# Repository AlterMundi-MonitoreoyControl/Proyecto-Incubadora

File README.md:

# LibreIncu 

[Manual de montaje](docs/index.md) · [Descargar PDF](docs/manual_libreincu_150.pdf)

Is an innovative project aimed at enhancing the efficiency and productivity of poultry incubators in family farming. Developed by Asociación Civil AlterMundi and CTO, this system integrates advanced monitoring and control technologies to optimize temperature and humidity levels, reducing manual labor and increasing hatch rates. Utilizing free hardware and software, the project promotes sustainable agricultural practices and empowers local communities with technical skills. Join us in revolutionizing family farming with technology!

Each incubator broadcasts a Wi-Fi network with a name that starts with “incu-” followed by a number. A user who wants to control their incubator can connect to this Wi-Fi network and change the incubator paramteres using the android app. Additionally, each incubator also connects to an external Wi-Fi network to send data over the internet to a remote Grafana server.

## LibreIncu en los medios
Aquí encontrarás enlaces a 

### Notas y artículos periodísticos 
Tiempo Argentino.Tiempo Rural.

Crean “LibreIncu”, una incubadora para familias productoras que funciona con software libre
https://bit.ly/LibreIncu

Pagina 12.

Problemas en la salud, maltrato animal y pérdida de soberanía. ¿Qué hacer con la industria avícola?
https://www.pagina12.com.ar/798691-que-hacer-con-la-industria-avicola

Multimedio Comechingones: 

INCUBADORAS LIBRES Y LA SOBERANÍA ALIMENTARIA Y TECNOLÓGICA.
https://www.youtube.com/watch?v=XAIEJV1IsmM

Radio Pueblo 103.3

Somos Tierra (programa) 07/03
“LibreIncu”, una incubadora para familias productoras que funciona con software libre.
https://www.facebook.com/100064102022746/posts/pfbid0N8CtLHdo2AVj12pVsAtcoeShCmByB2GCyXqmLqw75aoo8GYHFhkMTCCCVQQF8PBvl/?app=fbl

CDM Noticias: 

👉🏽En una entrevista radial con CDM Noticias, Fabricio Puzio, integrante de la organización rural CTO y uno de los impulsores del proyecto, brindó detalles del proyecto
https://cdmnoticias.com.ar/2025/03/11/libreincu-una-incubadora-de-pollos-con-software-libre-para-la-agricultura-familiar-en-cordoba/

### Videos

En este video encontrarán las voces de las comunidades que recibieron la incubadora en 1ra persona:
Youtube: https://youtu.be/KnWVigydmrw
Drive (para descarga archivo):
https://drive.google.com/file/d/1XJGJvUBiZXpjTJCaMYPYS3Le8TjS4YHT/view?usp=drive_link

Este video resume la actividad de febrero de 2025, dónde se realizó una capacitación técnica sobre el uso de la incubadora y su entrega a las comunidades:
Youtube: https://youtu.be/x1D_cCt7HYg
Drive (archivo):
https://drive.google.com/file/d/1NNPJ5_CfbWtDd18YyunTMB_yW_l8wr9t/view?usp=drive_link

En este video, encontrarán las voces del Equipo de Altermundi, reflexionando sobre el proceso de desarrollo.
Youtube: https://youtu.be/SZky4Ak8hUw
Drive (archivo):
https://drive.google.com/file/d/1BhJ7BwKUeTCceVNzBBIgxEsvleegejvH/view?usp=drive_link

En este video encontrarán testimonios sobre lo que implica el proyecto de desarrollo para las organizaciones involucradas.
Youtube: https://youtu.be/OzdKqgwdBYY

En este video encontrarán una presentación técnica Incubadora, con sus componentes:
https://www.youtube.com/watch?v=WrC1Y-ACtMo
Corte cuadrado 1:
https://drive.google.com/file/d/1Y_UQ-bno3-HFeVKtA_xg6CsesUtA-4hE/view?usp=drive_link
Corte cuadrado 2:
https://drive.google.com/file/d/13rHx7xk9e1rThg5PIM3QHikm3YS5sNPg/view?usp=drive_link

En este video encontrarán testimonios sobre la 1er Capacitación realizada con las comunidades sobre manejo productivo de huevos fértiles e incubadora.
https://youtu.be/IfGGvOIJ1b8
https://drive.google.com/file/d/1ajWQofPJQxNfXo5LtOdFrOzkCoTbWGiC/view?usp=sharing

## made with :heart: by:

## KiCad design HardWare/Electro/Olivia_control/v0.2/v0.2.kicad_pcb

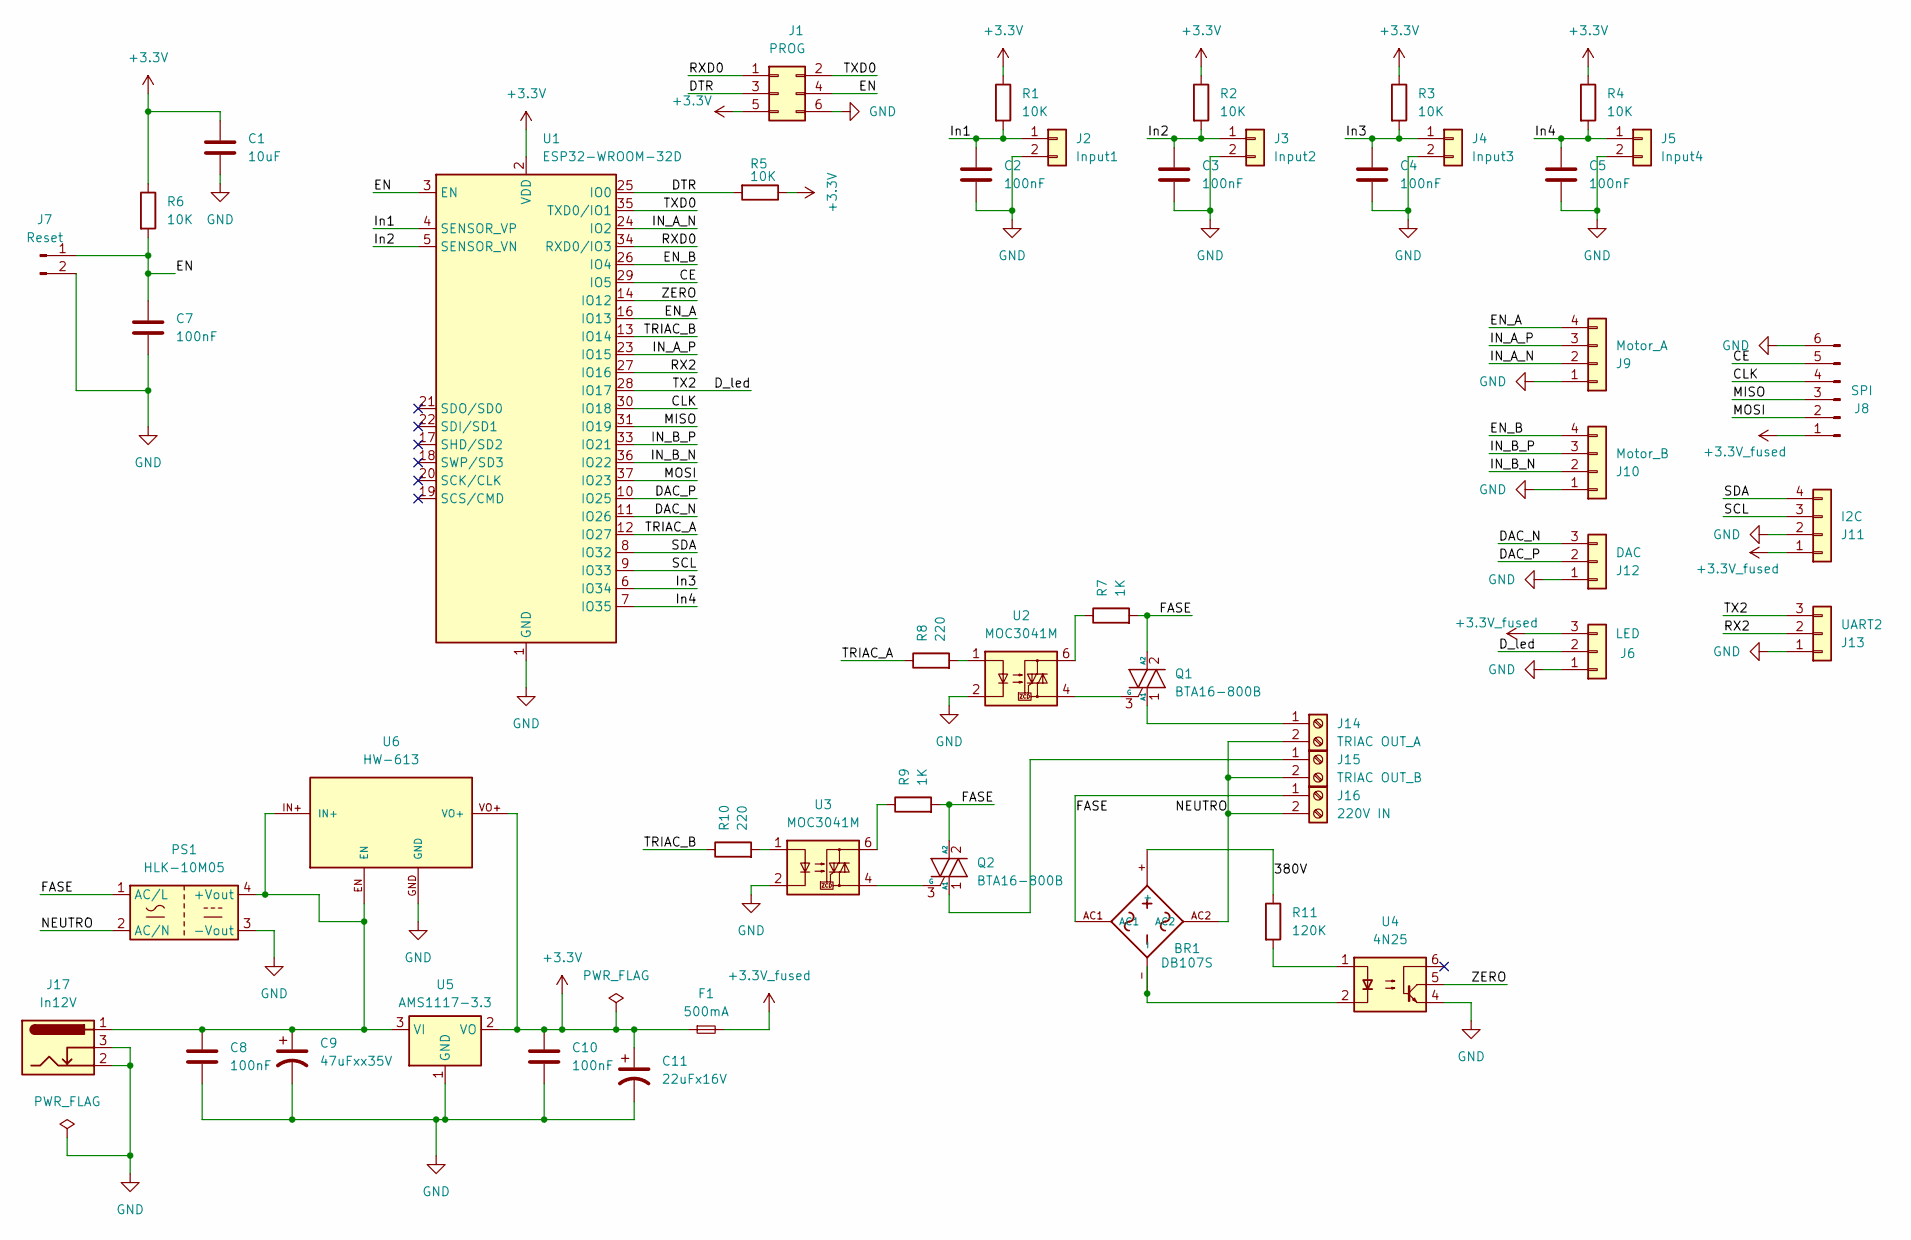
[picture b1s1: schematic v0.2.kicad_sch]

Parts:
BR1: DB107S; DIOB_DB107S; DigiKey_Part_Number 1655-DB107STR-ND
C1: 10uF; C_0805_2012Metric_Pad1.18x1.45mm_HandSolder
C2, C3, C4, C5, C7, C8, C10: 100nF; C_0805_2012Metric_Pad1.18x1.45mm_HandSolder
C9: 47uFxx35V; CP_EIA-6032-28_Kemet-C_Pad2.25x2.35mm_HandSolder
C11: 22uFx16V; CP_EIA-6032-28_Kemet-C_Pad2.25x2.35mm_HandSolder
F1: 500mA; Fuse_1206_3216Metric_Pad1.42x1.75mm_HandSolder
J1: PROG; PinHeader_2x03_P2.54mm_Vertical
J2: Input1; Molex_SL_171971-0002_1x02_P2.54mm_Vertical
J3: Input2; Molex_SL_171971-0002_1x02_P2.54mm_Vertical
J4: Input3; Molex_SL_171971-0002_1x02_P2.54mm_Vertical
J5: Input4; Molex_SL_171971-0002_1x02_P2.54mm_Vertical
J6: LED; Molex_SL_171971-0003_1x03_P2.54mm_Vertical
J7: Reset; PinHeader_1x02_P2.54mm_Vertical
J8: SPI; PinHeader_1x06_P2.54mm_Vertical
J9: Motor_A; Molex_SL_171971-0004_1x04_P2.54mm_Vertical
J10: Motor_B; Molex_SL_171971-0004_1x04_P2.54mm_Vertical
J11: I2C; Molex_SL_171971-0004_1x04_P2.54mm_Vertical
J12: DAC; Molex_SL_171971-0003_1x03_P2.54mm_Vertical
J13: UART2; Molex_SL_171971-0003_1x03_P2.54mm_Vertical
J14: TRIAC OUT_A; PhoenixContact_GMSTBA_2,5_2-G-7,62_1x02_P7.62mm_Horizontal
J15: TRIAC OUT_B; PhoenixContact_GMSTBA_2,5_2-G-7,62_1x02_P7.62mm_Horizontal
J16: 220V IN; PhoenixContact_GMSTBA_2,5_2-G-7,62_1x02_P7.62mm_Horizontal
J17: In12V; BarrelJack_Horizontal
PS1: HLK-10M05; Converter_ACDC_Hi-Link_HLK-10Mxx
Q1, Q2: BTA16-800B; TO-220-3_Vertical
R1, R2, R3, R4, R5, R6: 10K; R_0805_2012Metric_Pad1.20x1.40mm_HandSolder
R7, R9: 1K; R_0805_2012Metric_Pad1.20x1.40mm_HandSolder
R8, R10: 220; R_0805_2012Metric_Pad1.20x1.40mm_HandSolder
R11: 120K; R_0805_2012Metric_Pad1.20x1.40mm_HandSolder
U1: ESP32-WROOM-32D
U2, U3: MOC3041M; SMDIP-6_W9.53mm
U4: 4N25; SMDIP-6_W9.53mm
U5: AMS1117-3.3; SOT-223-3_TabPin2
U6: HW-613

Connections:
+3.3V: C1.1, C10.1, C11.1, F1.1, J1.5, R1.1, R2.1, R3.1, R4.1, R5.1, R6.1, U1.2 (VDD), U5.2 (VO), U6.VO+
+3.3V_fused: F1.2, J6.3, J8.1, J11.1
/380V: BR1.+, R11.1
/CE: J8.5, U1.29 (IO5)
/CLK: J8.4, U1.30 (IO18)
/DAC_N: J12.3, U1.11 (IO26)
/DAC_P: J12.2, U1.10 (IO25)
/DTR: J1.3, R5.2, U1.25 (IO0)
/D_led: J6.2, J13.3, U1.28 (IO17)
/EN: C7.1, J1.4, J7.1, R6.2, U1.3 (EN)
/EN_A: J9.4, U1.16 (IO13)
/EN_B: J10.4, U1.26 (IO4)
/FASE: BR1.AC1, J16.1, PS1.1 (AC/L), Q1.2 (A2), Q2.2 (A2), R7.2, R9.2
/IN_A_N: J9.2, U1.24 (IO2)
/IN_A_P: J9.3, U1.23 (IO15)
/IN_B_N: J10.2, U1.36 (IO22)
/IN_B_P: J10.3, U1.33 (IO21)
/In1: C2.1, J2.1, R1.2, U1.4 (SENSOR_VP)
/In2: C3.1, J3.1, R2.2, U1.5 (SENSOR_VN)
/In3: C4.1, J4.1, R3.2, U1.6 (IO34)
/In4: C5.1, J5.1, R4.2, U1.7 (IO35)
/MISO: J8.3, U1.31 (IO19)
/MOSI: J8.2, U1.37 (IO23)
/NEUTRO: BR1.AC2, J14.2, J15.2, J16.2, PS1.2 (AC/N)
/RX2: J13.2, U1.27 (IO16)
/RXD0: J1.1, U1.34 (RXD0/IO3)
/SCL: J11.3, U1.9 (IO33)
/SDA: J11.4, U1.8 (IO32)
/TRIAC_A: R8.1, U1.12 (IO27)
/TRIAC_B: R10.1, U1.13 (IO14)
/TXD0: J1.2, U1.35 (TXD0/IO1)
/ZERO: U1.14 (IO12), U4.5, U4.6
GND: C1.2, C2.2, C3.2, C4.2, C5.2, C7.2, C8.2, C9.2, C10.2, C11.2, J1.6, J2.2, J3.2, J4.2, J5.2, J6.1, J7.2, J8.6, J9.1, J10.1, J11.2, J12.1, J13.1, J17.2, J17.3, PS1.3 (-Vout), U1.1 (GND), U1.15 (GND), U1.38 (GND), U1.39 (GND), U2.2, U3.2, U4.4, U5.1 (GND), U6.GND
unnamed: J14.1, Q1.1 (A1)
unnamed: J15.1, Q2.1 (A1)
unnamed: C8.1, C9.1, J17.1, PS1.4 (+Vout), U5.3 (VI), U6.EN, U6.IN+
unnamed: Q1.3 (G), U2.4
unnamed: Q2.3 (G), U3.4
unnamed: R7.1, U2.6
unnamed: R8.2, U2.1
unnamed: R9.1, U3.6
unnamed: R10.2, U3.1
unnamed: R11.2, U4.1

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
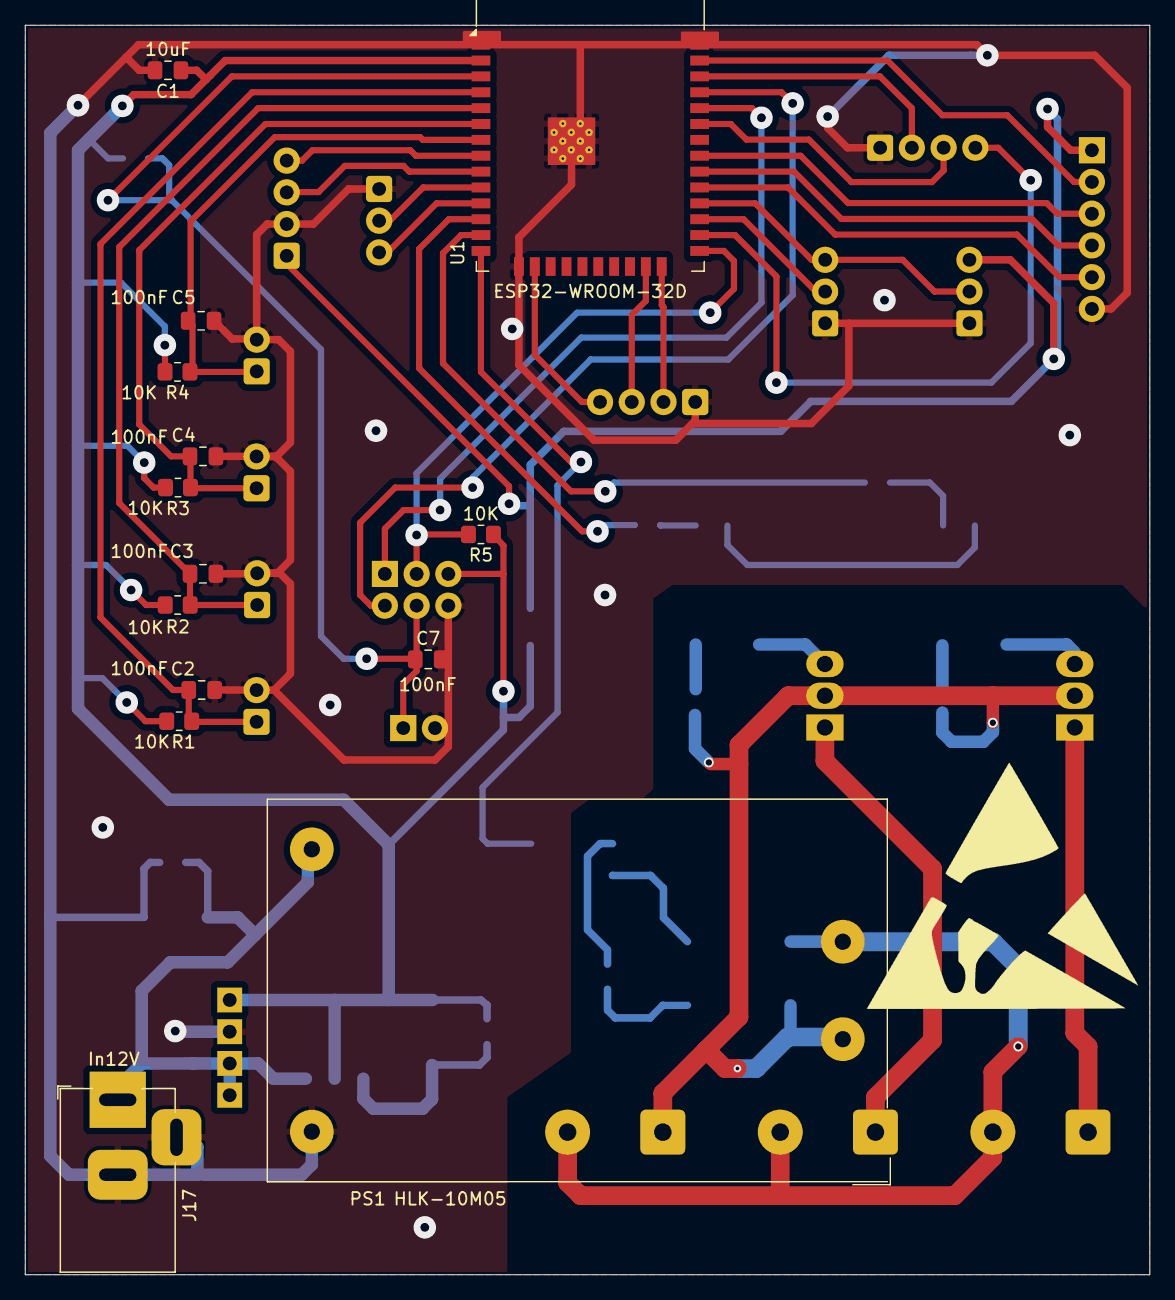
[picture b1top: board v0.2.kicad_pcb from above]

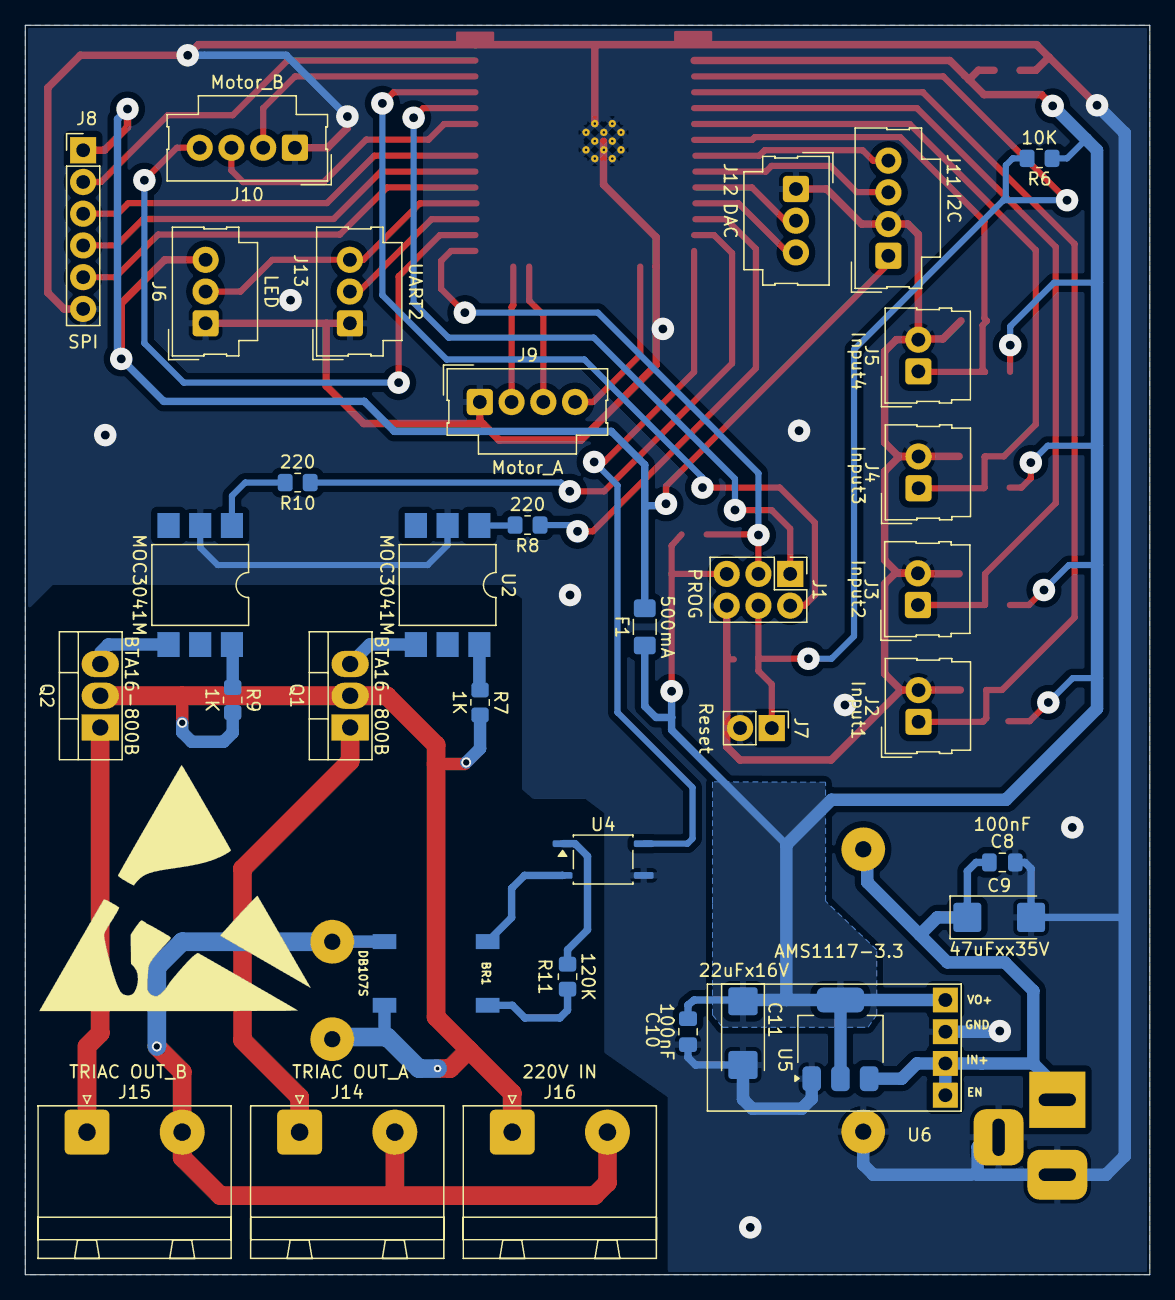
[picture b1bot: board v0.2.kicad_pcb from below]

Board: 2 copper layers, 90.0 x 100.0 mm, 49 parts (35 on the bottom side), 44 nets.

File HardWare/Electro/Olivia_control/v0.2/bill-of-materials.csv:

"Reference","Value","Footprint","Qty"
"BR1","DB107S","lib:DIOB_DB107S","1"
"C1","10uF","Capacitor_SMD:C_0805_2012Metric_Pad1.18x1.45mm_HandSolder","1"
"C2,C3,C4,C5,C7,C8,C10","100nF","Capacitor_SMD:C_0805_2012Metric_Pad1.18x1.45mm_HandSolder","7"
"C9","47uFxx35V","Capacitor_Tantalum_SMD:CP_EIA-6032-28_Kemet-C_Pad2.25x2.35mm_HandSolder","1"
"C11","22uFx16V","Capacitor_Tantalum_SMD:CP_EIA-6032-28_Kemet-C_Pad2.25x2.35mm_HandSolder","1"
"F1","500mA","Fuse:Fuse_1206_3216Metric_Pad1.42x1.75mm_HandSolder","1"
"J1","PROG","Connector_PinHeader_2.54mm:PinHeader_2x03_P2.54mm_Vertical","1"
"J2","Input1","Connector_Molex:Molex_SL_171971-0002_1x02_P2.54mm_Vertical","1"
"J3","Input2","Connector_Molex:Molex_SL_171971-0002_1x02_P2.54mm_Vertical","1"
"J4","Input3","Connector_Molex:Molex_SL_171971-0002_1x02_P2.54mm_Vertical","1"
"J5","Input4","Connector_Molex:Molex_SL_171971-0002_1x02_P2.54mm_Vertical","1"
"J6","LED","Connector_Molex:Molex_SL_171971-0003_1x03_P2.54mm_Vertical","1"
"J7","Reset","Connector_PinHeader_2.54mm:PinHeader_1x02_P2.54mm_Vertical","1"
"J8","SPI","Connector_PinHeader_2.54mm:PinHeader_1x06_P2.54mm_Vertical","1"
"J9","Motor_A","Connector_Molex:Molex_SL_171971-0004_1x04_P2.54mm_Vertical","1"
"J10","Motor_B","Connector_Molex:Molex_SL_171971-0004_1x04_P2.54mm_Vertical","1"
"J11","I2C","Connector_Molex:Molex_SL_171971-0004_1x04_P2.54mm_Vertical","1"
"J12","DAC","Connector_Molex:Molex_SL_171971-0003_1x03_P2.54mm_Vertical","1"
"J13","UART2","Connector_Molex:Molex_SL_171971-0003_1x03_P2.54mm_Vertical","1"
"J14","TRIAC OUT_A","Connector_Phoenix_GMSTB:PhoenixContact_GMSTBA_2,5_2-G-7,62_1x02_P7.62mm_Horizontal","1"
"J15","TRIAC OUT_B","Connector_Phoenix_GMSTB:PhoenixContact_GMSTBA_2,5_2-G-7,62_1x02_P7.62mm_Horizontal","1"
"J16","220V IN","Connector_Phoenix_GMSTB:PhoenixContact_GMSTBA_2,5_2-G-7,62_1x02_P7.62mm_Horizontal","1"
"J17","In12V","Connector_BarrelJack:BarrelJack_Horizontal","1"
"Q1,Q2","BTA16-800B","Package_TO_SOT_THT:TO-220-3_Vertical","2"
"R1,R2,R3,R4,R5,R6","10K","Resistor_SMD:R_0805_2012Metric_Pad1.20x1.40mm_HandSolder","6"
"R7,R9","1K","Resistor_SMD:R_0805_2012Metric_Pad1.20x1.40mm_HandSolder","2"
"R8,R10","220","Resistor_SMD:R_0805_2012Metric_Pad1.20x1.40mm_HandSolder","2"
"R11","120K","Resistor_SMD:R_0805_2012Metric_Pad1.20x1.40mm_HandSolder","1"
"U1","ESP32-WROOM-32D","RF_Module:ESP32-WROOM-32D","1"
"U2,U3","MOC3041M","Package_DIP:SMDIP-6_W9.53mm","2"
"U4","4N25","Package_DIP:SMDIP-6_W9.53mm","1"
"U6","HW-613","Connector_PinHeader_2.54mm:PinHeader_1x04_P2.54mm_Vertical","1"

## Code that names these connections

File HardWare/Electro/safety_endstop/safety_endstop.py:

#!/usr/bin/env python3
"""Esquemas del final de carrera de seguridad para el motor de volteo.

Agrega DOS finales de carrera (NC, normalmente cerrados) en serie con las
entradas logicas IN1 e IN2 del puente H, en paralelo a los reed switches que
ya usa el firmware (GPIO35 / GPIO34). Es un enclavamiento por HARDWARE: corta
la marcha aunque el firmware o el reed fallen (sobre-recorrido).

Comportamiento DIRECCIONAL:
  - FC-SUP (tope superior) corta IN1 (subir) y deja libre IN2 (bajar).
  - FC-INF (tope inferior) corta IN2 (bajar) y deja libre IN1 (subir).
  => al pisar un tope el motor NO avanza en esa direccion pero puede revertir
     para salir del fin de carrera.

Genera SVG con schemkit (repo vecino). Correr con el venv de schemkit:
    /home/pablo/repos/schemkit/.venv/bin/python safety_endstop.py
"""

import os
import sys

# schemkit (repo vecino) — agregar su raiz por si no esta instalado en el venv
sys.path.insert(0, '/home/pablo/repos/schemkit')

import schemdraw
import schemdraw.elements as elm
from schemdraw import flow

from schemkit import (
    CONFIG, add_title, add_footer,
    C_GPIO, C_VCC, C_GND, C_WARN, C_ADC, NOTE_COLOR,
)

OUT = os.path.join(os.path.dirname(os.path.abspath(__file__)), 'schematics')
os.makedirs(OUT, exist_ok=True)


# ---------------------------------------------------------------------------
# 1. Enclavamiento de seguridad: corte direccional de IN1 / IN2
# ---------------------------------------------------------------------------
def draw_safety_interlock():
    with schemdraw.Drawing(file=os.path.join(OUT, 'sch_safety_endstop.svg'),
                           show=False) as d:
        d.config(**CONFIG)

        # === ESP32 — 3 salidas hacia el puente H ===
        esp = d.add(elm.Ic(
            pins=[
                elm.IcPin(name='IN_A_N', anchorname='IN1', side='right', slot='3/3'),
                elm.IcPin(name='IN_A_P', anchorname='IN2', side='right', slot='2/3'),
                elm.IcPin(name='EN_A',   anchorname='EN',  side='right', slot='1/3'),
            ],
            edgepadW=2.8, edgepadH=1.2, pinspacing=3.4, lsize=11,
        ).label('Motor_A / J9\n(placa Olivia)', loc='center', fontsize=10))

        # GPIO de origen (en el ESP32) que sale por cada pin del conector Motor_A
        d.add(elm.Label().at((esp.IN1[0] - 0.3, esp.IN1[1] + 0.55))
              .label('pin2 · GPIO2', fontsize=7, color=NOTE_COLOR, halign='right'))
        d.add(elm.Label().at((esp.IN2[0] - 0.3, esp.IN2[1] + 0.55))
              .label('pin3 · GPIO15', fontsize=7, color=NOTE_COLOR, halign='right'))
        d.add(elm.Label().at((esp.EN[0] - 0.3, esp.EN[1] + 0.55))
              .label('pin4 · EN_A', fontsize=7, color=NOTE_COLOR, halign='right'))

        # === Puente H — alineado pin a pin con el ESP32 ===
        GAP = 11
        hb = d.add(elm.Ic(
            pins=[
                elm.IcPin(name='IN1',  anchorname='HIN1', side='left',  slot='3/3'),
                elm.IcPin(name='IN2',  anchorname='HIN2', side='left',  slot='2/3'),
                elm.IcPin(name='EN',   anchorname='HEN',  side='left',  slot='1/3'),
                elm.IcPin(name='OUT1', anchorname='OUT1', side='right', slot='2/2'),
                elm.IcPin(name='OUT2', anchorname='OUT2', side='right', slot='1/2'),
            ],
            edgepadW=1.2, edgepadH=1.2, pinspacing=3.4, lsize=11,
        ).at((esp.IN1[0] + GAP, esp.IN1[1])).anchor('HIN1')
         .label('Puente H\n(modulo)', loc='center', fontsize=10))

        # --- Helper: tramo IN con final de carrera NC + pull-down ---
        def in_line_with_endstop(esp_pin, hb_pin, fc_label, in_label):
            seg = 2.8          # tramo ESP -> switch
            sw_len = 1.9       # largo del switch
            # tramo desde el pin del ESP
            d.add(elm.Line().at(esp_pin).right(seg).color(C_GPIO)
                  .label(in_label, loc='top', fontsize=8))
            # final de carrera NC (normalmente cerrado) en serie
            sw = d.add(elm.Switch(nc=True).right().length(sw_len).color(C_WARN)
                       .label(fc_label, loc='top', fontsize=8, color=C_WARN))
            node = sw.end
            d.add(elm.Dot().at(node))
            # continua hasta la entrada del puente H
            d.add(elm.Line().at(node).tox(hb_pin[0]).color(C_GPIO))
            # pull-down 10k: deja la entrada en 0 (motor parado) si el FC abre.
            # Cae dentro del hueco bajo su propia linea (no cruza las demas).
            d.add(elm.Resistor().at(node).down(1.6)
                  .label('10k', loc='right', fontsize=8))
            d.add(elm.Ground())
            return node

        # IN1 = IN_A_N (J9 pin2, subir): cortado por el tope SUPERIOR
        in_line_with_endstop(esp.IN1, hb.HIN1, 'FC-SUP (NC)', 'IN_A_N  subir')
        # IN2 = IN_A_P (J9 pin3, bajar): cortado por el tope INFERIOR
        in_line_with_endstop(esp.IN2, hb.HIN2, 'FC-INF (NC)', 'IN_A_P  bajar')

        # EN — directo (sin corte; el corte va solo en IN1/IN2)
        d.add(elm.Line().at(esp.EN).to(hb.HEN).color(C_GPIO)
              .label('EN  habilita', loc='bottom', fontsize=8))

        # === Motor de volteo en OUT1/OUT2 ===
        mx = hb.OUT1[0] + 3.0
        d.add(elm.Line().at(hb.OUT1).right(3.0).color(C_VCC))
        d.add(elm.Line().at(hb.OUT2).right(3.0).color(C_GND))
        d.add(elm.Motor().at((mx, hb.OUT1[1])).down().toy(hb.OUT2[1])
              .label('M\nvolteo', loc='right', fontsize=9))

        add_footer(
            d,
            'Finales de carrera NORMALMENTE CERRADOS (NC) en serie con IN1/IN2  +  pull-down 10k a GND.\n'
            'En reposo el FC esta cerrado -> la senal de control (conector Motor_A) llega al puente H. Al pisar el tope\n'
            '(o si se corta el cable) el FC abre -> el pull-down fuerza esa entrada a 0 -> el puente H deja de empujar.\n'
            'DIRECCIONAL: FC-SUP corta IN1 (subir) y FC-INF corta IN2 (bajar); la direccion opuesta sigue libre para revertir.\n'
            'Es independiente del firmware: actua aunque el reed o el ESP32 fallen. EN_A (J9 pin4) no se corta.')
        add_title(d, 'Final de carrera de seguridad — corte direccional de IN1/IN2')

    print('  OK sch_safety_endstop.svg')


# ---------------------------------------------------------------------------
# 2. Contexto: reed switches (sensado por firmware) vs FC (corte por HW)
# ---------------------------------------------------------------------------
def draw_context():
    with schemdraw.Drawing(file=os.path.join(OUT, 'sch_reeds_vs_endstop.svg'),
                           show=False) as d:
        d.config(**CONFIG)

        # Eje de recorrido vertical
        x_axis = 0
        y_top, y_bot = 3.3, -3.3
        d.add(elm.Line().at((x_axis, y_top)).to((x_axis, y_bot)).color(NOTE_COLOR))
        d.add(elm.Label().at((x_axis, y_top + 0.5)).label('SUBIR', fontsize=9,
              color=NOTE_COLOR, halign='center'))
        d.add(elm.Label().at((x_axis, y_bot - 0.5)).label('BAJAR', fontsize=9,
              color=NOTE_COLOR, halign='center'))

        def stop_pair(y, reed_txt, reed_color, fc_txt, cut_txt):
            d.add(elm.Dot().at((x_axis, y)))
            # Reed (sensor, firmware) a la izquierda
            d.add(elm.Line().at((x_axis, y)).left(1.8).color(reed_color))
            d.add(elm.SwitchReed().left().length(1.8).color(reed_color)
                  .label(reed_txt, loc='top', fontsize=8, color=reed_color))
            d.add(elm.Label().at((x_axis - 5.7, y - 0.05))
                  .label('LEE GPIO\n(sensa)', fontsize=7,
                         color=NOTE_COLOR, halign='center'))
            # Final de carrera (corte HW) a la derecha
            d.add(elm.Line().at((x_axis, y)).right(1.8).color(C_WARN))
            d.add(elm.Switch(nc=True).right().length(1.8).color(C_WARN)
                  .label(fc_txt, loc='top', fontsize=8, color=C_WARN))
            d.add(elm.Label().at((x_axis + 5.6, y - 0.05))
                  .label(cut_txt, fontsize=7, color=C_WARN, halign='center'))

        stop_pair(2.0, 'Reed UP\nGPIO35', C_ADC,
                  'FC-SUP (NC)', 'CORTA IN1\n(subir)')
        stop_pair(-2.0, 'Reed DOWN\nGPIO34', C_ADC,
                  'FC-INF (NC)', 'CORTA IN2\n(bajar)')

        add_footer(
            d,
            'reed (izq.): el firmware lo LEE para frenar en el punto normal.\n'
            'FC de seguridad (der.): apenas mas alla, CORTA IN1/IN2 por hardware.\n'
            'Si el reed o el firmware fallan, el FC frena igual el motor.')
        add_title(d, 'Dos capas por extremo: reed (sensa) + FC (corta)')

    print('  OK sch_reeds_vs_endstop.svg')


if __name__ == '__main__':
    print('Generando esquemas del final de carrera de seguridad...')
    draw_safety_interlock()
    draw_context()
    print(f'\nListo. SVG en {OUT}/')

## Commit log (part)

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2024-04-05 added files from original repository
2024-04-05 agrego carpeta HardWare
2024-04-10 added mobile-app content
2024-04-10 changed folder name
2024-04-17 changes that allow the app to run and debug
2024-04-18 Remove unnecesary files
2024-04-18 add linux folder as ignorable
2024-05-04 Add advances in new json fields
2024-05-04 Remove deprecated parameters
2024-06-07 Add new fields and logic to the API
2024-07-08 Add Advances in Humidifier controller
2024-07-12 Add Advances in humidifier_control
2024-07-22 Add Humidity Control Tested
2024-07-24 Add Fabri Config
2024-07-26 Test Fabri Config
2024-08-15 Fix leak memory logs
2024-10-15 Add humidifier update
2024-10-28 data adapted to fw
2024-11-10 Fix incubator name can be changed with POST REQUEST
2024-11-10 Fix WiFi bug
2024-11-10 Add Advances in notification
2024-11-14 INICIALES is incubator.incubator_name now
2024-11-14 Fix wifiinit.lua
2024-11-14 Fix wifiinit.lua W.station_cfg
2024-11-15 Now notifications sent to Grafana are sent to ntfy
2024-11-21 Fix incubator_name
2024-11-22 notifications tests
2024-11-26 Add 10 more characters in hash and incubator_name
2024-11-26 Add 10 more characters in hash and incubator_name/hash
2024-11-29 revert fix incubator name
2024-11-29 Revert "Fix incubator_name"
    This reverts commit 2a3086a579ac3e68a0a622822c5e46fdb33094b2.
2024-11-29 add 10 characters in incubator name and incubator hash
2024-11-29 add 15 characters in incubator name and incubator hash
2024-12-16 remove inc useless
2024-12-20 Add ntfy messages as error in logs
2024-12-20 Add ap_name handler
2024-12-20 Fix tab iden
2024-12-21 add reboot timer to avoid tansmision stop
2024-12-21 fix timer call
2024-12-22 fix reboot time to one hour
2025-01-27 wifi ap change name
2025-02-11 added logic to allow to edit rotation_period
2025-03-19 ordeno y elimino archivos HardWare
2025-03-19 Create LICENSE
    CERN OHL
2025-05-06 Update TESTING.md
    add other pin initialization
2025-06-06 Reemplazo de Conector 220V por borneras 7,62mm.
2025-06-07 Cambio de medidas de huecos y pads para llevar a proceso de fabricación industrial. La version original tiene margenes de tolerancia adaptados a las impresiciones de la fabricación manual.
2025-06-07 Cambio de despeje de zonas para llevar a proceso de fabricación industrial. La version original tiene margenes de tolerancia adaptados a las impresiciones de la fabricación manual.
2025-06-07 Añadida serigrafía para fabricación industrial.
2025-06-08 Pequenos fixes en sector 220V. Imagenes de vista, Gerbers y pdf de esquematico generados. Limpieza.
2025-06-12 Added soldering mask to gerber outputs.
2025-07-02 added structural plans
2025-08-03 Add fabrication specs.
2025-08-13 Update incubator.lua
    tiempos y temp humidificador
2025-08-14 Update TESTING.md
    improve sensor testing
2025-08-14 fix rotation test; lua is single process and the previous timings could not be met
2025-08-20 add throttle and memory check
2025-08-20 throttle by message with random interval
2025-08-21 Mesaages change, so the previous version didn throtle. Now we have throtling by type and throtling by server
2025-08-21 fix error and improve log
2025-08-21 add simple and clear
2025-08-21 fix intial value error
2025-08-21 fix reporting add all errors to the queue
2025-08-21 handle ntp date renewal
2025-08-21 improve diff
2025-10-21 replaced 4N25 with TLP181
2026-03-10 improve logging and fix time comparison
2026-04-08 add uptime and change throle in grafana messages
2026-04-09 fix error400 in send to grafana
2026-04-23 Upgrade upload-artifact action
2026-05-12 fix debounce
2026-05-13 temp: add push trigger for CI validation on fork branch
2026-05-13 revert: remove temp push trigger
2026-05-28 add names and fix 12v lines
2026-05-28 agregar documentación
